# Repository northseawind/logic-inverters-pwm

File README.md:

# logic-inverters-pwm

## Description
Device can be used as a simple non-MCU PWM generator with variable duty cycle (and frequency, if you replace this one potentiometer with two - one between 1-2 points (look at the diagram) and second between 3-2). Combined with powerful switch it can be applied directly to power on some heavy load. Example application is an autonomous (battery-powered) LED holiday lights driver. If the voltage needed for lights is in a tolerance range of CD4069 you don't need any external converter. The frequency is fixed with value about 1-10 kHz.

## Notes
Potentiometer(s) placement on PCB is optional - as you can take it out from the board and locate somewhere else on the device' case, it's not necessary to make exactly this holes on the board.

PCB was made firstly for the manual manufacturing so tracks widths are not meaningful and serve illustrative purposes.

## Tuning
For many loads such as my LED lights the relationship between duty cycle and brightness is nonlinear. So you need more accurate and precise tuning on one end and more rough on another. For this case you need to play with constant and variable resistances to find the suitable balance. You can use nonlinear (logarithmic) potentiometers.

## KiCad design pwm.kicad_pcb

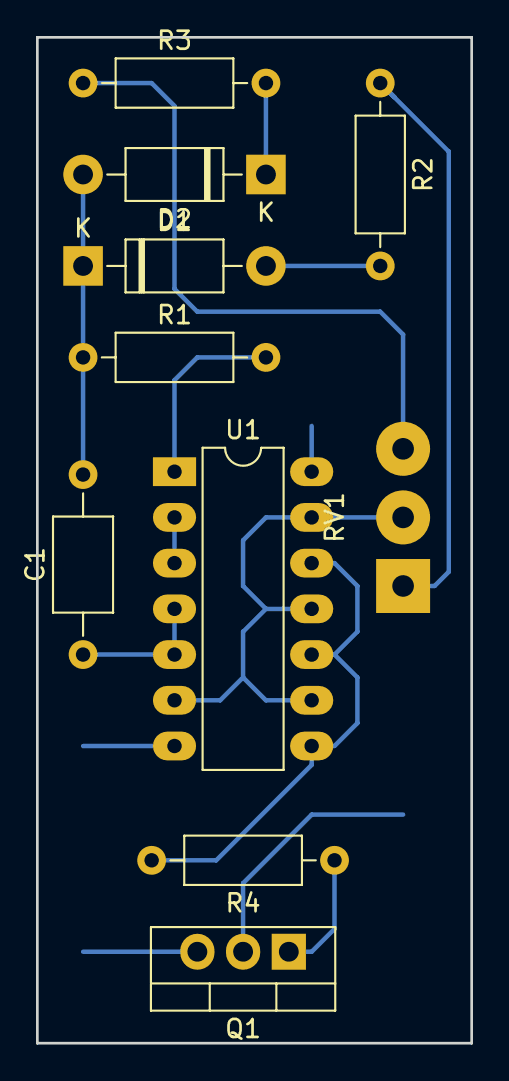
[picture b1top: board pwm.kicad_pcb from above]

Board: 2 copper layers, 24.1 x 55.9 mm, 10 parts (0 on the bottom side), 12 nets.

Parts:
C1: 0.033 uF; C_Axial_L5.1mm_D3.1mm_P10.00mm_Horizontal
D1, D2: 1N4004; D_DO-41_SOD81_P10.16mm_Horizontal
Q1: IRF540N; TO-220-3_Vertical
R1, R2, R3: 1k; R_Axial_DIN0207_L6.3mm_D2.5mm_P10.16mm_Horizontal
R4: 50; R_Axial_DIN0207_L6.3mm_D2.5mm_P10.16mm_Horizontal
RV1: R_POT; SolderWirePad_1x03_P3.81mm_Drill1.2mm
U1: 4069; DIP-14_W7.62mm_LongPads

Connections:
Earth: Q1.3, U1.7
unnamed: C1.1, U1.4, U1.5
unnamed: C1.2, D1.1, D2.2, R1.1
unnamed: D1.2, R2.2
unnamed: D2.1, R3.2
unnamed: Q1.1, R4.1
unnamed: R1.2, U1.1
unnamed: R2.1, RV1.1
unnamed: R3.1, RV1.3
unnamed: R4.2, U1.8, U1.10, U1.12
unnamed: RV1.2, U1.6, U1.9, U1.11, U1.13
unnamed: U1.2, U1.3

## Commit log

2018-12-20 Add README, add preview images
